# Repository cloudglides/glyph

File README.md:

# Glyph

## What is it?

its a techwear keychain, designed with alot of things in mind including the holy drip. pretty much a blinky with a chase pattern

## why

- it is cool
- holy drip
- i never made a blinky

## how does it work

it uses a 555 ic with another ic for the chase pattern, pretty basic on the surface

## motivation

i saw alot of techwear but they are hella expensive so i decided to make my own oss version!

## pcb overview

### all layers

### f.cu

### b.cu

## assembly

1. get the pcb manufactured
2. solder all the components according to the schematic
3. double check everything and power it on
4. enjoy the holy drip

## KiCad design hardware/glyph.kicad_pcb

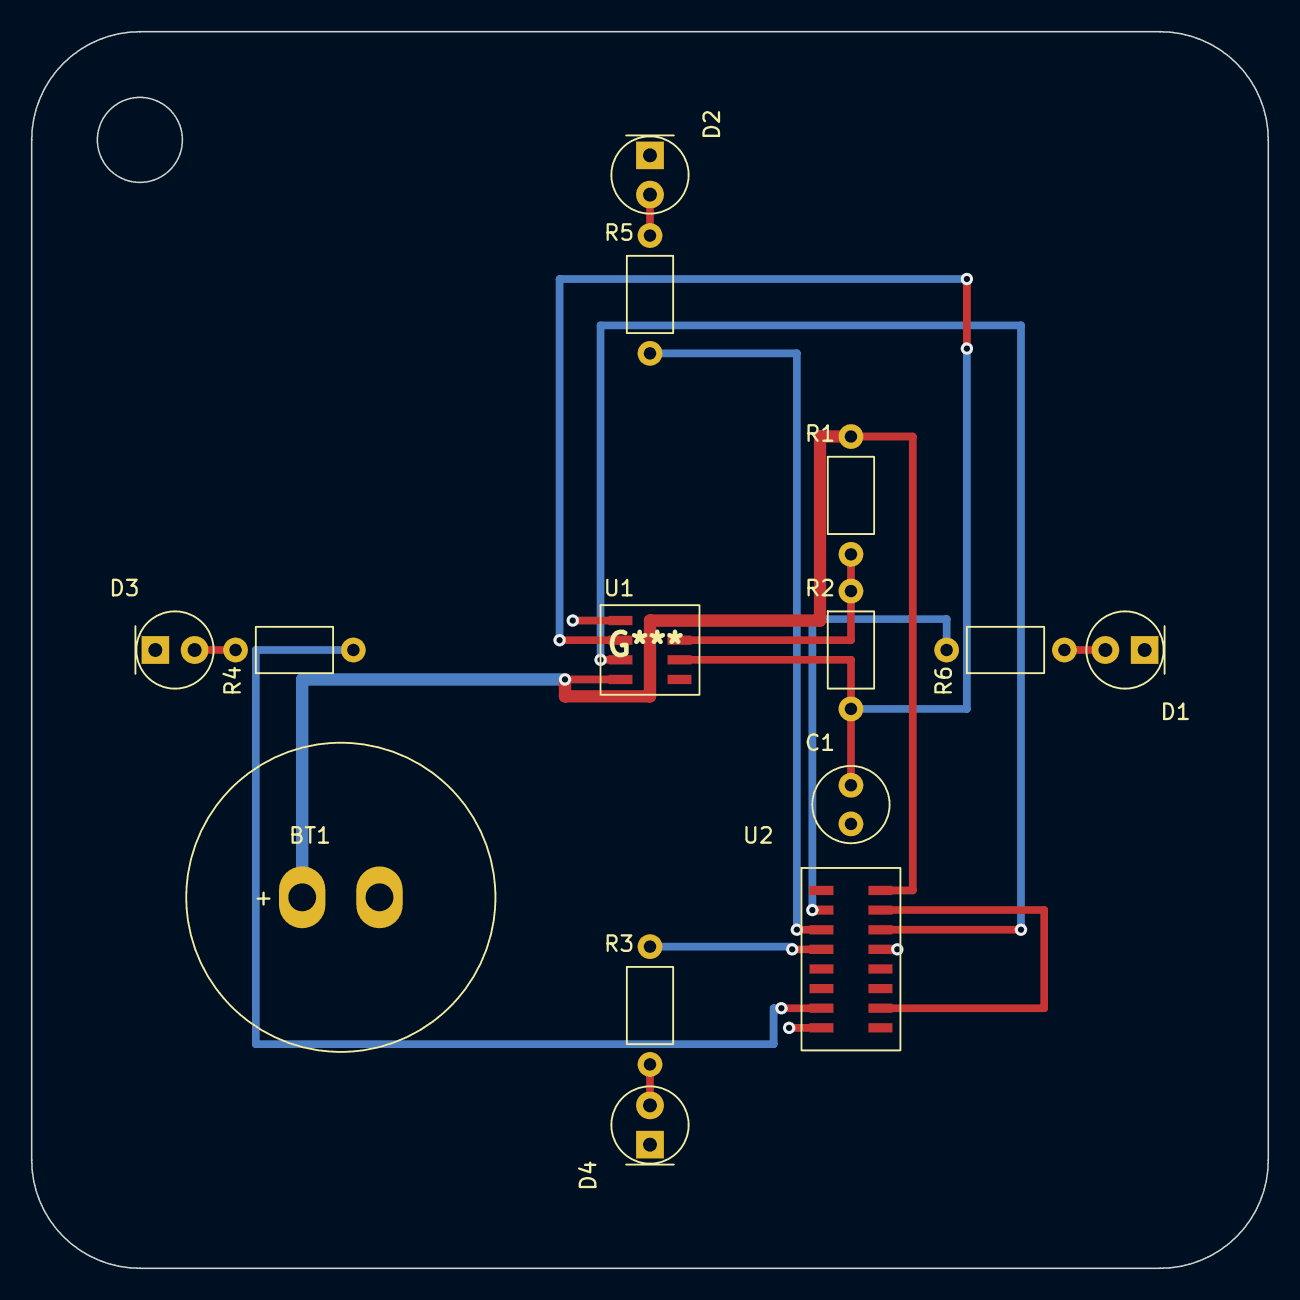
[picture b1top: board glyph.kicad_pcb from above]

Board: 2 copper layers, 80.0 x 80.0 mm, 14 parts (0 on the bottom side), 14 nets.

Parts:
BT1: Battery_Cell; BatteryHolder_Keystone_3002_1x2032
C1: 0.1uF; C_Disc_D5.0mm_W2.5mm_P2.50mm
D1, D2, D3, D4: LED; LED_D5.0mm
R1: 1k; R_Axial_DIN0207_L6.3mm_D2.5mm_P7.62mm_Horizontal
R2: 680k; R_Axial_DIN0207_L6.3mm_D2.5mm_P7.62mm_Horizontal
R3, R4, R5, R6: 330; R_Axial_DIN0207_L6.3mm_D2.5mm_P7.62mm_Horizontal
U1: ICM7555xB; SOIC-8_3.9x4.9mm_P1.27mm
U2: 4017; SOIC-16_3.9x9.9mm_P1.27mm

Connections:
GND: BT1.2, C1.2, D1.1, D2.1, D3.1, D4.1, U1.1, U2.8, U2.13
unnamed: BT1.1, R1.1, U1.4, U1.8, U2.16
unnamed: D1.2, R6.2
unnamed: D2.2, R5.1
unnamed: D3.2, R4.1
unnamed: D4.2, R3.2
unnamed: R1.2, R2.1, U1.7
unnamed: U1.3, U2.14
unnamed: C1.1, R2.2, U1.2, U1.6
unnamed: R5.2, U2.3
unnamed: R6.1, U2.2
unnamed: R3.1, U2.4
unnamed: R4.2, U2.7
unnamed: U2.10, U2.15

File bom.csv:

Reference,Component,Value,Qty,Unit Price (USD),Total Price (USD),LCSC Part #,Notes
U1,ICM7555xB (555 timer),CMOS 555 SOIC-8,1,0.2334,0.2334,C6986,TI TLC555CDR
U2,4017 decade counter,CD4017 SOIC-16,1,0.7334,0.7334,C11349,TI CD4017BM96
BT1,battery holder,CR2032 SMD clip,1,0.0495,0.0495,C70373,QIJEY CR2032 3V (Keystone 3002 equivalent)
C1,capacitor,0.1uF 5mm disc,1,0.0800,0.0800,C3034534,verify LCSC part for 0.1uF 5mm disc; price is estimate
D1,LED,5mm red 20mA,1,0.2238,0.2238,C7151892,Kingbright WP7113SURC
D2,LED,5mm red 20mA,1,0.2238,0.2238,C7151892,Kingbright WP7113SURC
D3,LED,5mm red 20mA,1,0.2238,0.2238,C7151892,Kingbright WP7113SURC
D4,LED,5mm red 20mA,1,0.2238,0.2238,C7151892,Kingbright WP7113SURC
R1,resistor,1k 1/4W axial,1,0.0200,0.0200,C17630,metal film 1/4W axial; verify exact LCSC part
R2,resistor,680k 1/4W axial,1,0.0200,0.0200,C17630,metal film 1/4W axial; verify exact LCSC part
R3,resistor,330 1/4W axial,1,0.0200,0.0200,C17630,metal film 1/4W axial; verify exact LCSC part
R4,resistor,330 1/4W axial,1,0.0200,0.0200,C17630,metal film 1/4W axial; verify exact LCSC part
R5,resistor,330 1/4W axial,1,0.0200,0.0200,C17630,metal film 1/4W axial; verify exact LCSC part
R6,resistor,330 1/4W axial,1,0.0200,0.0200,C17630,metal film 1/4W axial; verify exact LCSC part
TOTAL,,,,,2.1115,,
